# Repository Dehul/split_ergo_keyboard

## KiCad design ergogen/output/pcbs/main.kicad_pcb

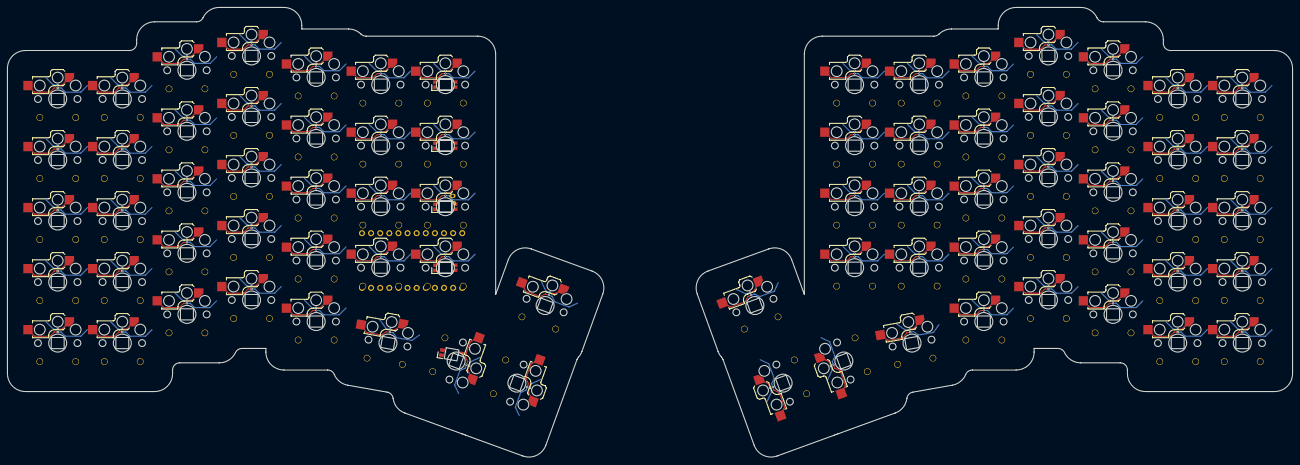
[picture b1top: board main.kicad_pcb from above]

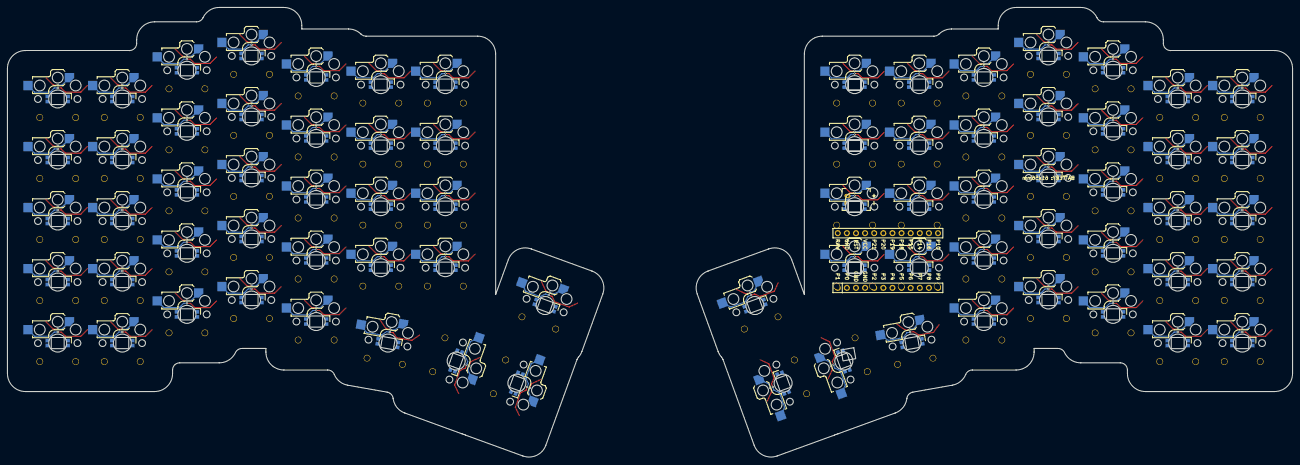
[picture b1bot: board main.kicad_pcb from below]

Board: 2 copper layers, 358.0 x 125.2 mm, 155 parts (150 on the bottom side), 4 nets.

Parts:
JST1: battery_connector_jst_ph_2
LED1, LED2, LED3, LED4, LED5, LED6, LED7, LED8, LED9, LED10, LED11, LED12, LED13, LED14, LED15, LED16, LED17, LED18, LED19, LED20, LED21, LED22, LED23, LED24, LED25, LED26, LED27, LED28, LED29, LED30, LED31, LED32, LED33, LED34, LED35, LED36, LED37, LED38, LED39, LED40, LED41, LED42, LED43, LED44, LED45, LED46, LED47, LED48, LED49, LED50, LED51, LED52, LED53, LED54, LED55, LED56, LED57, LED58, LED59, LED60, LED61, LED62, LED63, LED64, LED65, LED66, LED67, LED68, LED69, LED70, LED71, LED72, LED73, LED74, LED75, LED76, LED77, LED78, LED79: led_SK6812mini-e (per-keysingle-side)
MCU1: mcu_nice_nano
S1, S2, S3, S4, S5, S6, S7, S8, S9, S10, S11, S12, S13, S14, S15, S16, S17, S18, S19, S20, S21, S22, S23, S24, S25, S26, S27, S28, S29, S30, S31, S32, S33, S34, S35, S36, S37, S38, S39, S40, S41, S42, S43, S44, S45, S46, S47, S48, S49, S50, S51, S52, S53, S54, S55, S56, S57, S58, S59, S60, S61, S62, S63, S64, S65, S66, S67, S68, S69, S70, S71, S72, S73, S74: switch_choc_v1_v2

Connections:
DIN: LED1.2, LED2.2, LED3.2, LED4.2, LED5.2, LED6.2, LED7.2, LED8.2, LED9.2, LED10.2, LED11.2, LED12.2, LED13.2, LED14.2, LED15.2, LED16.2, LED17.2, LED18.2, LED19.2, LED20.2, LED21.2, LED22.2, LED23.2, LED24.2, LED25.2, LED26.2, LED27.2, LED28.2, LED29.2, LED30.2, LED31.2, LED32.2, LED33.2, LED34.2, LED35.2, LED36.2, LED37.2, LED38.2, LED39.2, LED40.2, LED41.2, LED42.2, LED43.2, LED44.2, LED45.2, LED46.2, LED47.2, LED48.2, LED49.2, LED50.2, LED51.2, LED52.2, LED53.2, LED54.2, LED55.2, LED56.2, LED57.2, LED58.2, LED59.2, LED60.2, LED61.2, LED62.2, LED63.2, LED64.2, LED65.2, LED66.2, LED67.2, LED68.2, LED69.2, LED70.2, LED71.2, LED72.2, LED73.2, LED74.2, LED75.2, LED76.2, LED77.2, LED78.2, LED79.2
DOUT: LED1.4, LED2.4, LED3.4, LED4.4, LED5.4, LED6.4, LED7.4, LED8.4, LED9.4, LED10.4, LED11.4, LED12.4, LED13.4, LED14.4, LED15.4, LED16.4, LED17.4, LED18.4, LED19.4, LED20.4, LED21.4, LED22.4, LED23.4, LED24.4, LED25.4, LED26.4, LED27.4, LED28.4, LED29.4, LED30.4, LED31.4, LED32.4, LED33.4, LED34.4, LED35.4, LED36.4, LED37.4, LED38.4, LED39.4, LED40.4, LED41.4, LED42.4, LED43.4, LED44.4, LED45.4, LED46.4, LED47.4, LED48.4, LED49.4, LED50.4, LED51.4, LED52.4, LED53.4, LED54.4, LED55.4, LED56.4, LED57.4, LED58.4, LED59.4, LED60.4, LED61.4, LED62.4, LED63.4, LED64.4, LED65.4, LED66.4, LED67.4, LED68.4, LED69.4, LED70.4, LED71.4, LED72.4, LED73.4, LED74.4, LED75.4, LED76.4, LED77.4, LED78.4, LED79.4
EXT_VCC: LED1.1, LED2.1, LED3.1, LED4.1, LED5.1, LED6.1, LED7.1, LED8.1, LED9.1, LED10.1, LED11.1, LED12.1, LED13.1, LED14.1, LED15.1, LED16.1, LED17.1, LED18.1, LED19.1, LED20.1, LED21.1, LED22.1, LED23.1, LED24.1, LED25.1, LED26.1, LED27.1, LED28.1, LED29.1, LED30.1, LED31.1, LED32.1, LED33.1, LED34.1, LED35.1, LED36.1, LED37.1, LED38.1, LED39.1, LED40.1, LED41.1, LED42.1, LED43.1, LED44.1, LED45.1, LED46.1, LED47.1, LED48.1, LED49.1, LED50.1, LED51.1, LED52.1, LED53.1, LED54.1, LED55.1, LED56.1, LED57.1, LED58.1, LED59.1, LED60.1, LED61.1, LED62.1, LED63.1, LED64.1, LED65.1, LED66.1, LED67.1, LED68.1, LED69.1, LED70.1, LED71.1, LED72.1, LED73.1, LED74.1, LED75.1, LED76.1, LED77.1, LED78.1, LED79.1
GND: JST1.1, LED1.3, LED2.3, LED3.3, LED4.3, LED5.3, LED6.3, LED7.3, LED8.3, LED9.3, LED10.3, LED11.3, LED12.3, LED13.3, LED14.3, LED15.3, LED16.3, LED17.3, LED18.3, LED19.3, LED20.3, LED21.3, LED22.3, LED23.3, LED24.3, LED25.3, LED26.3, LED27.3, LED28.3, LED29.3, LED30.3, LED31.3, LED32.3, LED33.3, LED34.3, LED35.3, LED36.3, LED37.3, LED38.3, LED39.3, LED40.3, LED41.3, LED42.3, LED43.3, LED44.3, LED45.3, LED46.3, LED47.3, LED48.3, LED49.3, LED50.3, LED51.3, LED52.3, LED53.3, LED54.3, LED55.3, LED56.3, LED57.3, LED58.3, LED59.3, LED60.3, LED61.3, LED62.3, LED63.3, LED64.3, LED65.3, LED66.3, LED67.3, LED68.3, LED69.3, LED70.3, LED71.3, LED72.3, LED73.3, LED74.3, LED75.3, LED76.3, LED77.3, LED78.3, LED79.3, MCU1.3, MCU1.4, MCU1.23
